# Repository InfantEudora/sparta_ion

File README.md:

Open Source Sparta ION
=============
There's a bunch of (Dutch) blog posts that go with this: (http://infant.tweakblogs.net/blog/cat/2875)

This repository contains the following:

 folder       |  descr
--------------|-------------------------------------------------------------
 eagle        | All relevant eagle files, BOM lists.
 ion_firmware | AVR Studio projects for the different kinds of firmware.
 ion_software | Software for testing, or uploading hex files.
 lib          | Files used in either firmware or software.
 lib_ion      | Files used for Sparta ION specific code.

All files in this repository are released under GNU GPLv3 (https://www.gnu.org/copyleft/gpl.html)

Software used:
----------------
 - Atmel Studio 6.1.2440 - BETA (http://www.atmel.com/microsite/atmel_studio6/)
 - GCC 4.9.2
 - Windows: Cygwin(https://cygwin.com/install.html)
 - Eagle 6.1.0 (http://www.cadsoftusa.com/)

Firmware:
----------------

The firmware running your bike's motor, consists of three parts:
 - A bootloader, started on powerup.
 - The actual firmware, called application executed by the bootloader.
 - Configuration memory, stored in ROM.

The bootloader uses two blocks to identify the harware it's running on, and what firmware should be loaded.
The firware uses one block to read/write settings, which are currently the strain gauge calibration.

If you wan't to build a control PCB, use the latest revision of 3phasecntrl.

New Hardare Revision Wishlist:
 - Crystal
 - ESD protection on HALL input. (REV2)

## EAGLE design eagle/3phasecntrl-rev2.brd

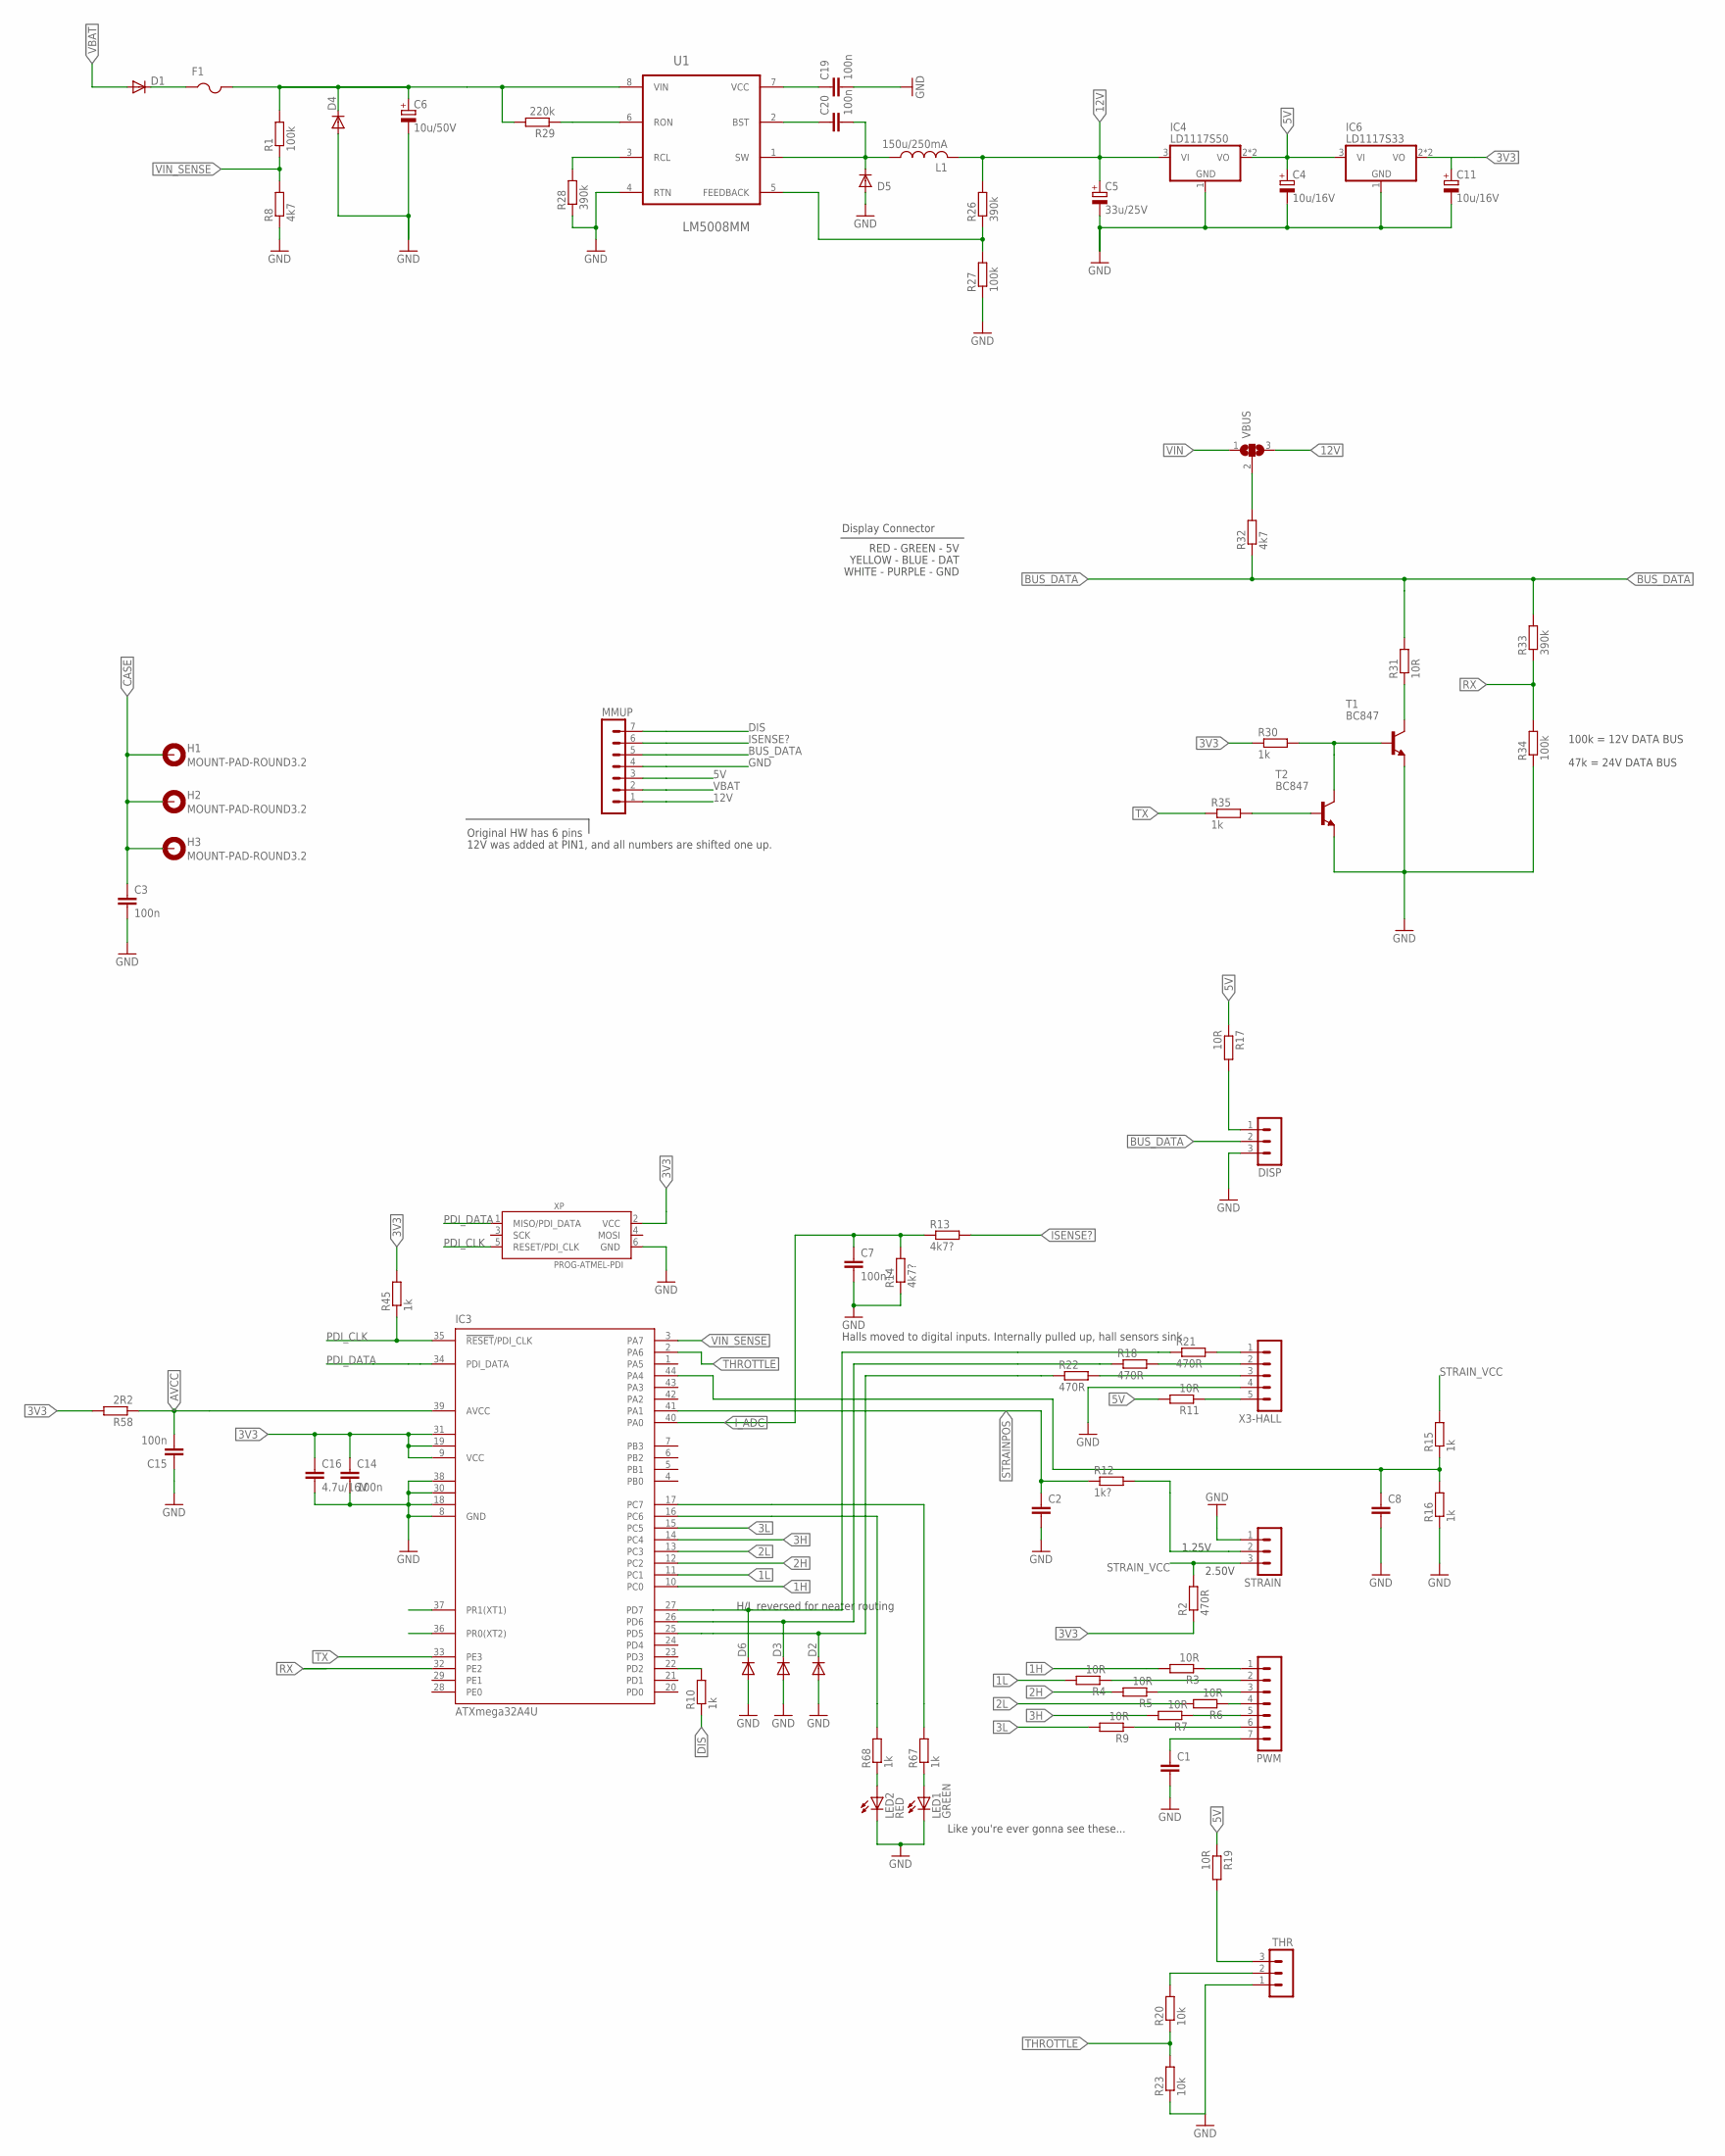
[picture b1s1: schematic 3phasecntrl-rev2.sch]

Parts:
C1, C2, C8: C-EUC0805K; C0805K
C3, C14, C15, C19, C20: 100n; C0805K
C4, C11: 10u/16V; 153CLV-0405
C5: 33u/25V; 153CLV-0605
C6: 10u/50V; 153CLV-0605
C7: 100n?; C0805K
C16: 4.7u/16V; C0805K
D1: BAT46WH; SMB; FARNELL 2069340
D2, D3, D6: PTVS3V3S1UTR; SOD123; FARNELL 2575110
D4: SM6T39A; SMB; FARNELL 9802703
D5: BAT46WH; SOD323-W
DISP: MA03-1
F1: PTCFUSE-1812; 1812
H1, H2, H3: MOUNT-PAD-ROUND3.2; 3,2-PAD
IC3: ATXmega32A4U; TQFP44
IC4: LD1117S50; SOT223; FARNELL 1467780
IC6: LD1117S33; SOT223
L1: 150u/250mA; POWER-CHOKE_WE-TPC
LED1: GREEN; CHIPLED_0805
LED2: RED; CHIPLED_0805
MMUP: MA07-1
PWM: MA07-1
R1, R27, R34: 100k; M0805
R2, R18, R21, R22: 470R; M0805
R3, R4, R5, R6, R7, R9, R11, R17, R19, R31: 10R; M0805
R8, R32: 4k7; M0805
R10, R15, R16, R30, R35, R67, R68: 1k; M0805
R12: 1k?; M0805
R13, R14: 4k7?; M0805
R20, R23: 10k; M0805
R26, R28, R33: 390k; M0805
R29: 220k; M0805
R45: 1k; R0805
R58: 2R2; R0805
STRAIN: MA03-1
T1, T2: BC847; SOT23
THR: MA03-1
U1: LM5008MM; SOP65P490X109-8N
VBUS: SJ2W; SJ_2
X3-HALL: MA05-1
XP: PROG-ATMEL-PDI; 6-LSTB2

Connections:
1H: IC3.10 (PC0), R3.2
1L: IC3.11 (PC1), R4.2
2H: IC3.12 (PC2), R5.2
2L: IC3.13 (PC3), R6.2
3H: IC3.14 (PC4), R7.2
3L: IC3.15 (PC5), R9.2
3V3: C11.+, C14.1, C16.1, IC3.9 (VCC), IC3.19 (VCC1), IC3.31 (VCC2), IC6.2 (VO), IC6.4 (VO), R2.1, R30.1, R45.2, R58.2, XP.2 (VCC)
5V: C4.+, IC4.2 (VO), IC4.4 (VO), IC6.3 (VI), MMUP.3, R11.2, R17.1, R19.1
12V: C5.+, IC4.3 (VI), L1.2, MMUP.1, R26.2, VBUS.3
AVCC: C15.2, IC3.39 (AVCC), R58.1
BUS_DATA: DISP.2, MMUP.5, R31.2, R32.1, R33.2
CASE: C3.1, H1.B3,2, H2.B3,2, H3.B3,2
DIS: MMUP.7, R10.1
GND: C1.2, C2.2, C3.2, C4.-, C5.-, C6.-, C7.2, C8.2, C11.-, C14.2, C15.1, C16.2, C19.2, D2.A, D3.A, D4.A, D5.A, D6.A, DISP.3, IC3.8 (GND), IC3.18 (GND1), IC3.30 (GND2), IC3.38 (GND3), IC4.1 (GND), IC6.1 (GND), LED1.C, LED2.C, MMUP.4, R8.1, R14.1, R16.1, R23.1, R27.1, R28.1, R34.1, STRAIN.1, T1.2 (E), T2.2 (E), THR.1, U1.4 (RTN), X3-HALL.4, XP.6 (GND)
ISENSE?: MMUP.6, R13.2
I_ADC: C7.1, IC3.40 (PA0), R13.1, R14.2
unnamed: C1.1, PWM.7
unnamed: D1.C, F1.1
unnamed: C19.1, U1.7 (VCC)
unnamed: PWM.1, R3.1
unnamed: R12.2, STRAIN.2
unnamed: R32.2, VBUS.2
unnamed: IC3.22 (PD2), R10.2
unnamed: R11.1, X3-HALL.5
unnamed: R21.2, X3-HALL.1
unnamed: PWM.2, R4.1
unnamed: R18.2, X3-HALL.2
unnamed: R31.1, T1.3 (C)
unnamed: R22.2, X3-HALL.3
unnamed: LED1.A, R67.1
unnamed: LED2.A, R68.1
unnamed: C20.1, U1.2 (BST)
unnamed: R19.2, THR.3
unnamed: D6.C, IC3.27 (PD7), R21.1
unnamed: IC3.16 (PC6), R68.2
unnamed: IC3.17 (PC7), R67.2
unnamed: C20.2, D5.C, L1.1, U1.1 (SW)
unnamed: R35.2, T2.1 (B)
unnamed: R26.1, R27.2, U1.5 (FEEDBACK)
unnamed: R30.2, T1.1 (B), T2.3 (C)
unnamed: D3.C, IC3.26 (PD6), R18.1
unnamed: R28.2, U1.3 (RCL)
unnamed: PWM.3, R5.1
unnamed: PWM.4, R6.1
unnamed: R29.1, U1.6 (RON)
unnamed: D2.C, IC3.25 (PD5), R22.1
unnamed: PWM.5, R7.1
unnamed: PWM.6, R9.1
unnamed: DISP.1, R17.2
PDI_CLK: IC3.35 (!RESET!/PDI_CLK), R45.1, XP.5 (RESET/PDI_CLK)
PDI_DATA: IC3.34 (PDI_DATA), XP.1 (MISO/PDI_DATA)
RX: IC3.32 (PE2), R33.1, R34.2
STRAINPOS: C2.1, IC3.41 (PA1), R12.1
STRAINREF: C8.1, IC3.44 (PA4), R15.1, R16.2
STRAIN_VCC: R2.2, R15.2, STRAIN.3
THIN: R20.2, THR.2
THROTTLE: IC3.2 (PA6), R20.1, R23.2
TX: IC3.33 (PE3), R35.1
VBAT: D1.A, MMUP.2
VIN: C6.+, D4.C, F1.2, R1.2, R29.2, U1.8 (VIN), VBUS.1
VIN_SENSE: IC3.3 (PA7), R1.1, R8.2

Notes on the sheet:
RED - GREEN - 5V
WHITE - PURPLE - GND
YELLOW - BLUE - DAT
1.25V
2.50V
Original HW has 6 pins
12V was added at PIN1, and all numbers are shifted one up.
Display Connector
H/L reversed for neater routing
Like you're ever gonna see these...
Halls moved to digital inputs. Internally pulled up, hall sensors sink.
100k = 12V DATA BUS
47k = 24V DATA BUS

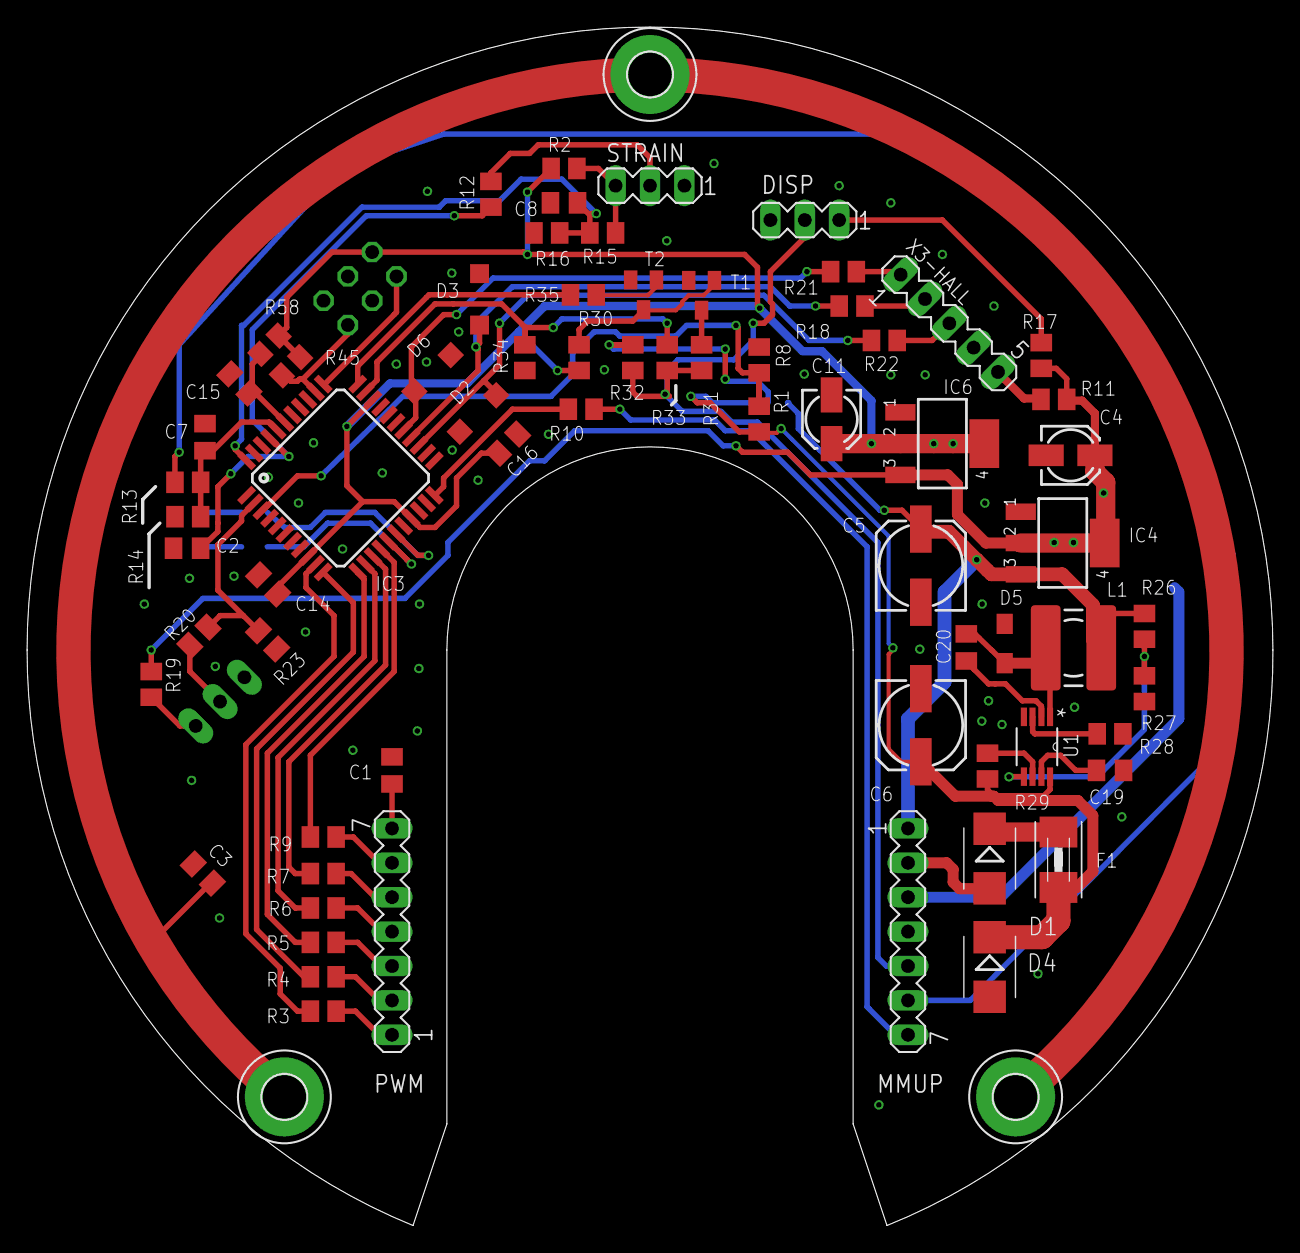
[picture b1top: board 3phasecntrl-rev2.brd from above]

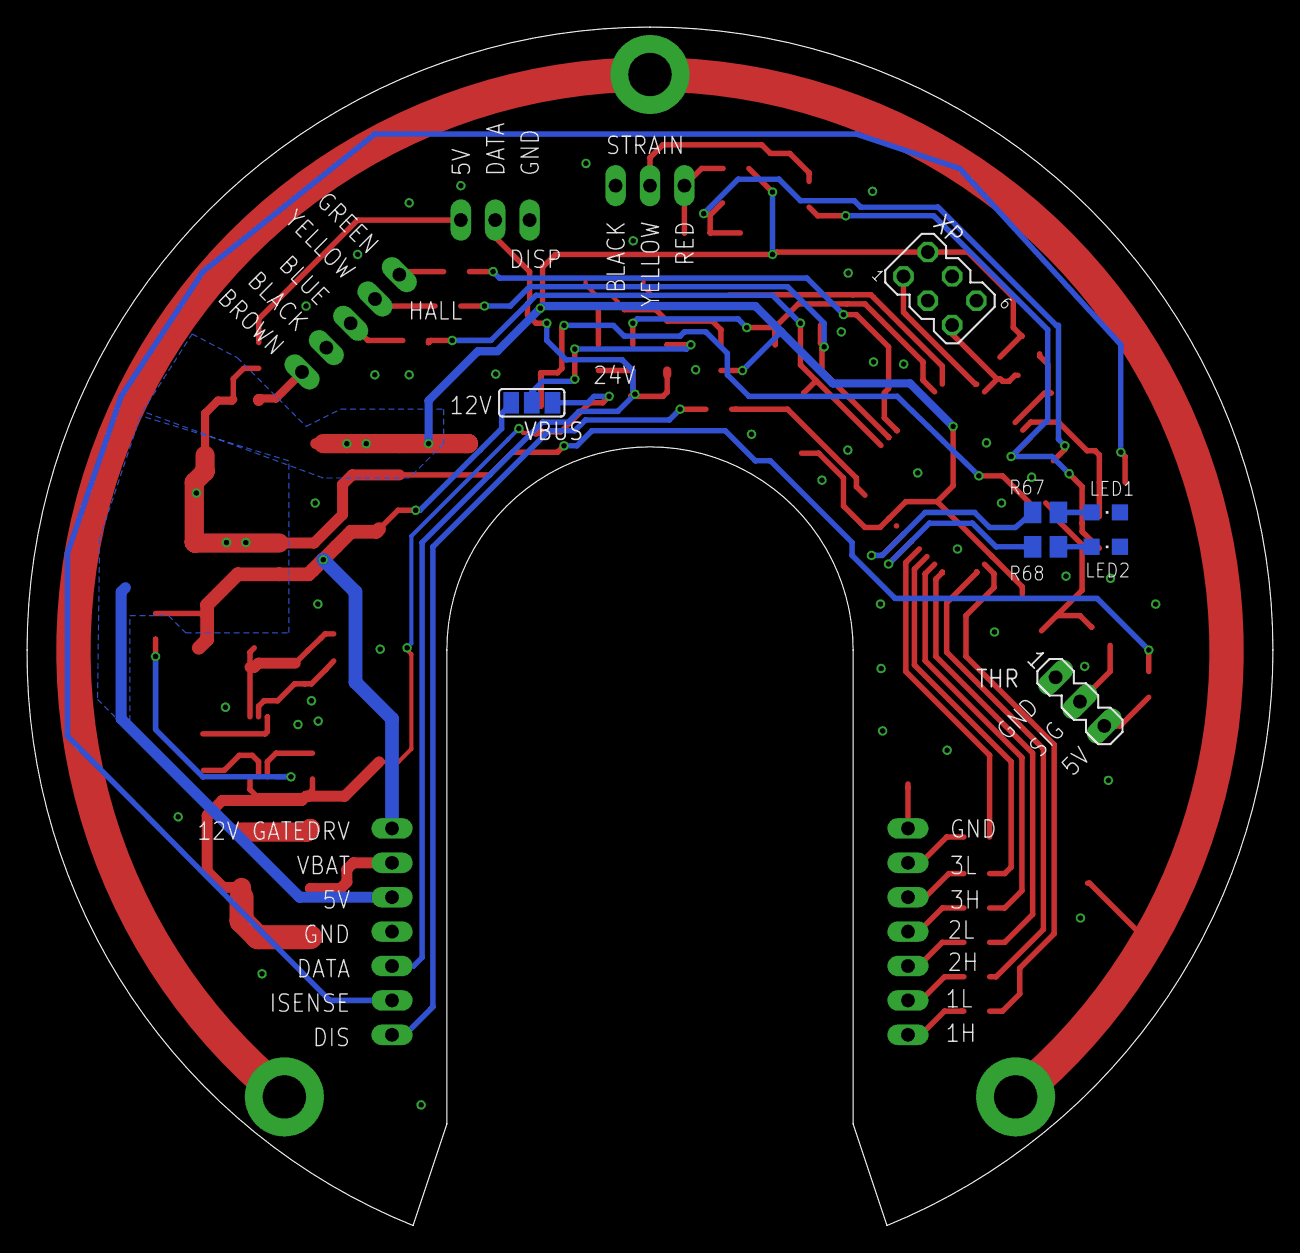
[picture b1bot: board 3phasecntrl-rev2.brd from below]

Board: 2 copper layers, 92.0 x 88.5 mm, 78 parts (7 on the bottom side), 61 nets.

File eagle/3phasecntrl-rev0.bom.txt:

Partlist exported from E:/IDE-E/Mijn Documenten/Projects/code/sparta_ion.git/eagle/3phasecntrl-rev0.sch at 4/5/2015 2:22:53 PM

Assembly variant: 

Qty Value              Device             Parts                              Farnell FarnellAlt1
1                      MA03-1             STRAIN                                                
1                      MA05-1             X3-HALL                                               
2                      MA07-1             MMUP, PWM                          1516283            
1                      SJ2W               VBUS                                                  
7   1k                 R-EU_M0805         R10, R12, R30, R35, R45, R67, R68  2078954            
1   2R2                R-EU_M0805         R58                                2078937            
1   4.7u/16V           C-EUC0805K         C16                                1759427            
4   4k7                R-EU_M0805         R8, R13, R14, R32                  2074469            
8   10R                R-EU_M0805         R3, R4, R5, R6, R7, R9, R11, R31   2073604            
2   10u/16V            CPOL-EU153CLV-0405 C4, C11                            9265554 9696920    
1   10u/50V            CPOL-EU153CLV-0605 C6                                 2068686            
1   68u/25V            CPOL-EU153CLV-0605 C5                                 2326209            
3   100k               R-EU_M0805         R1, R27, R34                       2073608            
8   100n               C-EUC0805K         C1, C2, C3, C7, C14, C15, C19, C20 2320839            
1   140mA              PTCFUSE-1812       F1                                 1345923            
1   150u/250mA         L-USWE-TPC         L1                                 2328764            
1   240k               R-EU_M0805         R29                                2139055            
3   390k               R-EU_M0805         R26, R28, R33                      9234322            
4   470R               R-EU_M0805         R2, R18, R21, R22                  2073777            
1   ATXmega32A4U       XMEGA16A4A         IC3                                2443192            
1   BAT46WH            DIODE-SOD323-W     D5                                 2069340            
2   BC847              BC847              T1, T2                             1081232            
1   GREEN              LEDCHIPLED_0805    LED1                               2290331            
1   LD1117S33          LM340ST-ST         IC6                                1467779            
1   LD1117S50          LM340ST-ST         IC4                                1467780            
1   LM5008MM           LM5008MM           U1                                 2112610            
3   MOUNT-PAD-ROUND3.2 MOUNT-PAD-ROUND3.2 H1, H2, H3                                            
1   PROG-ATMEL-PDI     PROG-ATMEL-PDI     XP                                                    
1   RED                LEDCHIPLED_0805    LED2                               1318244            
1   SM6T39A            DIODE-SMB          D4                                 9802703            
1   SS110B             DIODE-SMB          D1                                 1861422

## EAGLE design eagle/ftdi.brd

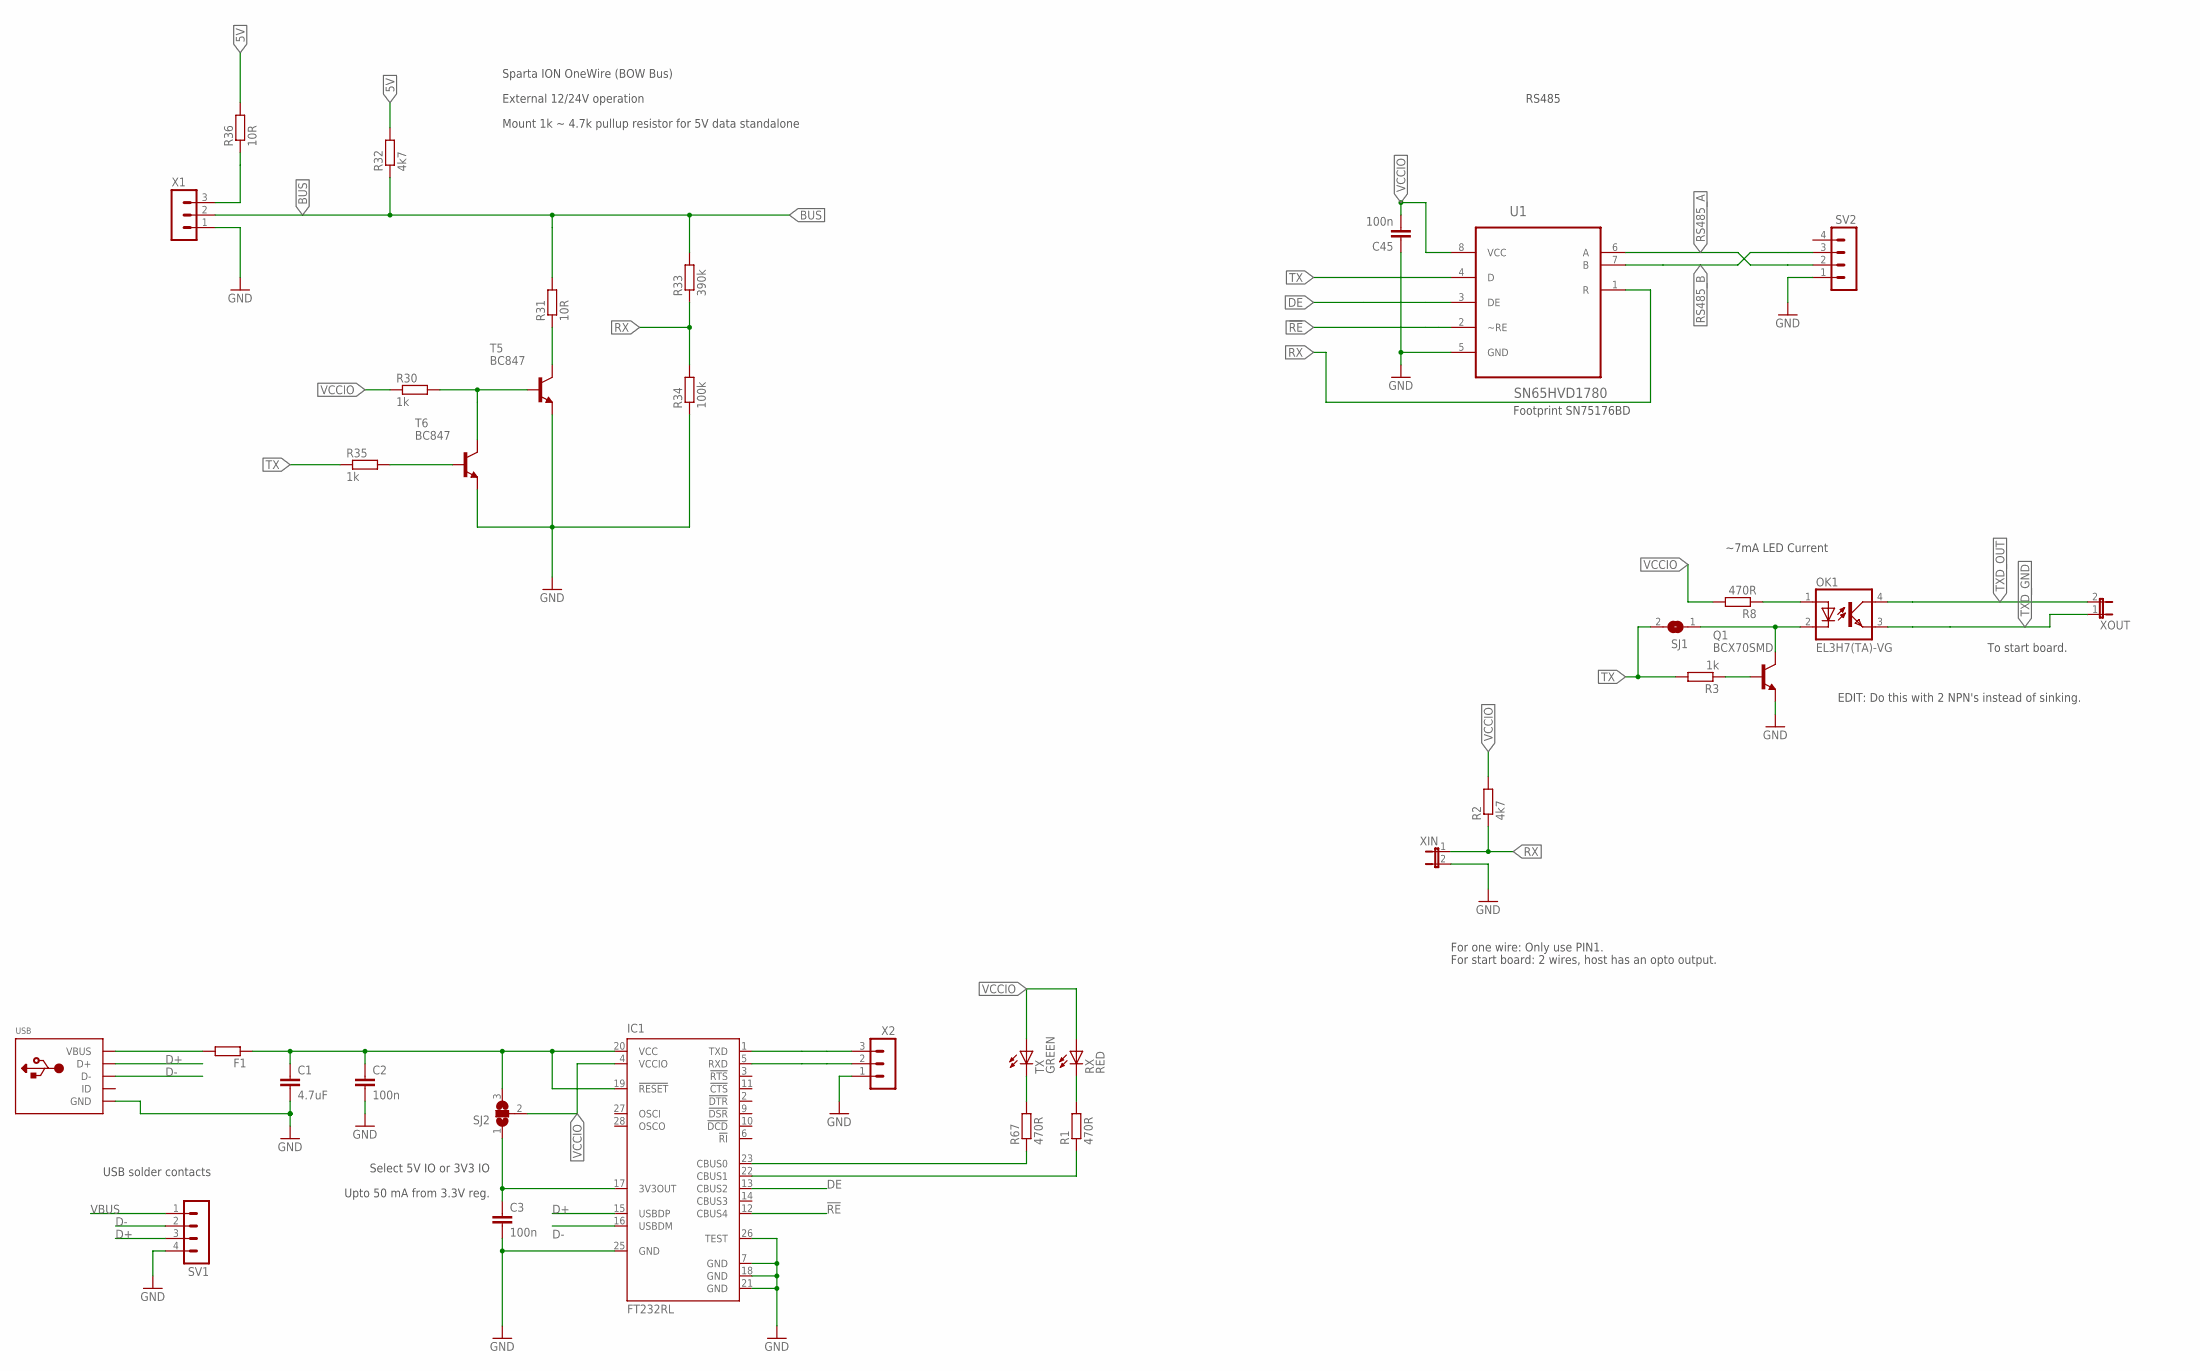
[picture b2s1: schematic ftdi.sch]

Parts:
C1: 4.7uF; C0805
C2, C3, C45: 100n; C0805
F1: R-EU_R0805; R0805
IC1: FT232RL; SSOP28
OK1: EL3H7(TA)-VG; MINI-FLAT-4
Q1: BCX70SMD; SOT23
R1, R67: 470R; M0805
R2: 4k7; R0805
R3: 1k; R0805
R8: 470R; R0805
R30, R35: 1k; M0805
R31, R36: 10R; M0805
R32: 4k7; M0805
R33: 390k; M0805
R34: 100k; M0805
RX: RED; CHIPLED_0805
SJ1: SJ
SJ2: SJ2W; SJ_2
SV1, SV2: MA04-1
T5, T6: BC847; SOT23
TX: GREEN; CHIPLED_0805
U1: SN65HVD1780; SOIC127P600X175-8N
USB: ADAFRUIT_USBMINIB; ADAFRUIT_USB-MINIB
X1, X2: MA03-1
XIN: JP1E; JP1
XOUT: JP1E; JP1

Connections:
5V: C1.1, C2.1, F1.1, IC1.19 (!RESET), IC1.20 (VCC), R32.2, R36.2, SJ2.3
!RE: IC1.12 (CBUS4), U1.2 (~RE)
BUS: R31.2, R32.1, R33.2, X1.2
D+: IC1.15 (USBDP), SV1.3, USB.D+
D-: IC1.16 (USBDM), SV1.2, USB.D-
DE: IC1.13 (CBUS2), U1.3 (DE)
GND: C1.2, C2.2, C3.2, C45.1, IC1.7 (GND), IC1.18 (GND), IC1.21 (GND), IC1.25 (GND), IC1.26 (TEST), Q1.2 (E), R34.1, SV1.4, SV2.1, T5.2 (E), T6.2 (E), U1.5 (GND), USB.GND, X1.1, X2.1, XIN.2
GND1: IC1.23 (CBUS0), R67.1
GND2: IC1.22 (CBUS1), R1.1
unnamed: C3.1, IC1.17 (3V3OUT), SJ2.1
unnamed: R1.2, RX.C
unnamed: OK1.2 (C), Q1.3 (C), SJ1.1
unnamed: OK1.1 (A), R8.1
unnamed: Q1.1 (B), R3.1
unnamed: R31.1, T5.3 (C)
unnamed: R35.2, T6.1 (B)
unnamed: R30.2, T5.1 (B), T6.3 (C)
unnamed: R36.1, X1.3
unnamed: R67.2, TX.C
RS485_A: SV2.2, U1.6 (A)
RS485_B: SV2.3, U1.7 (B)
RX: IC1.5 (RXD), R2.1, R33.1, R34.2, U1.1 (R), X2.2, XIN.1
TX: IC1.1 (TXD), R3.2, R35.1, SJ1.2, U1.4 (D), X2.3
TXD_GND: OK1.3 (EMIT), XOUT.1
TXD_OUT: OK1.4 (COL), XOUT.2
VBUS: F1.2, SV1.1, USB.VBUS
VCCIO: C45.2, IC1.4 (VCCIO), R2.2, R8.2, R30.1, RX.A, SJ2.2, TX.A, U1.8 (VCC)

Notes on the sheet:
Upto 50 mA from 3.3V reg.
Sparta ION OneWire (BOW Bus)
External 12/24V operation
Footprint SN75176BD
RS485
USB solder contacts
~7mA LED Current
To start board.
For one wire: Only use PIN1.
For start board: 2 wires, host has an opto output.
Mount 1k ~ 4.7k pullup resistor for 5V data standalone
Select 5V IO or 3V3 IO
EDIT: Do this with 2 NPN's instead of sinking.

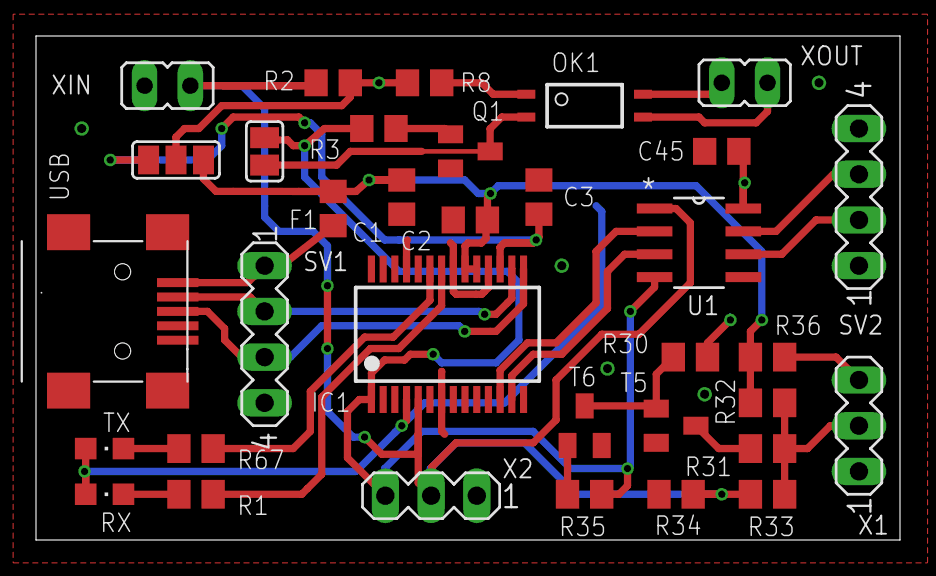
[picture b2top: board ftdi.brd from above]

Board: 2 copper layers, 48.0 x 28.0 mm, 34 parts (0 on the bottom side), 27 nets.

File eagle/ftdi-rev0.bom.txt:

Partlist exported from E:/IDE-E/Mijn Documenten/Projects/code/sparta_ion.git/eagle/ftdi.sch at 4/8/2015 5:38:11 PM

Assembly variant: 

Qty Value        Device            Parts             Farnell FarnellAlt1
1                ADAFRUIT_USBMINIB USB                                  
2                JP1E              XIN, XOUT                            
2                MA03-1            X1, X2                               
2                MA04-1            SV1, SV2                             
1                SJ                SJ1                                  
1                SJ2W              SJ2                                  
4   1k           R-EU_M0805        R3, R30, R32, R35 2078954            
1   2R2          R-EU_M0805        F1                2078937            
1   4.7u/16V     C-EUC0805K        C1                1759427            
1   4k7          R-EU_M0805        R2                2074469            
2   10R          R-EU_M0805        R31, R36          2073604            
1   100k         R-EU_M0805        R34               2073608            
3   100n         C-EUC0805K        C2, C3, C45       2320839            
1   390k         R-EU_M0805        R33               9234322            
3   470R         R-EU_M0805        R1, R8, R67       2073777            
3   BC847        BC847             T1, T5, T6        1081232            
1   EL3H7(TA)-VG TLP283            OK1                                  
1   FT232RL      FT232RL           IC1               1146032            
1   GREEN        LEDCHIPLED_0805   TX                2290331            
1   RED          LEDCHIPLED_0805   RX                1318244            
1   SN65HVD1780  SN75176BD         U1

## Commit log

2015-04-04 Readme
2015-04-05 Added farnell parts to eagledb file, BOM.
2015-04-06 Current regulation in steps of ~3 Amps. Strain calibration faster by holding it down, single button presses. Some typos fixed.
2015-04-08 PWM naming is intuitive: less is less, more is more. Strain signal is held at highest for a period. Implemented some FW_ features from app.h Roadlegal will now allow throttle override from middle but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
2015-04-12 Strain sensor with signed ad value, highest gain. Averaging moved, produced aliasing issues. Bootloader dind;t want to stay in bootload mode. Removed hex files from commit. Bom added
2015-04-12 Strain gain value in F5.
2015-04-12 Manual and connector partlist.
2017-05-07 Added retries on firmware load. Removed throttle by default.
2017-05-07 Rev. 2 board: Added throttle input, added 3 TVS on hall sensor
2017-05-07 Hall state in function1.6 PWM update uses buffer.
2017-05-07 ionloader user tty as first argument. use_throttle = true;
2017-05-09 Updated readme. Updated REV2 silkscreen.
